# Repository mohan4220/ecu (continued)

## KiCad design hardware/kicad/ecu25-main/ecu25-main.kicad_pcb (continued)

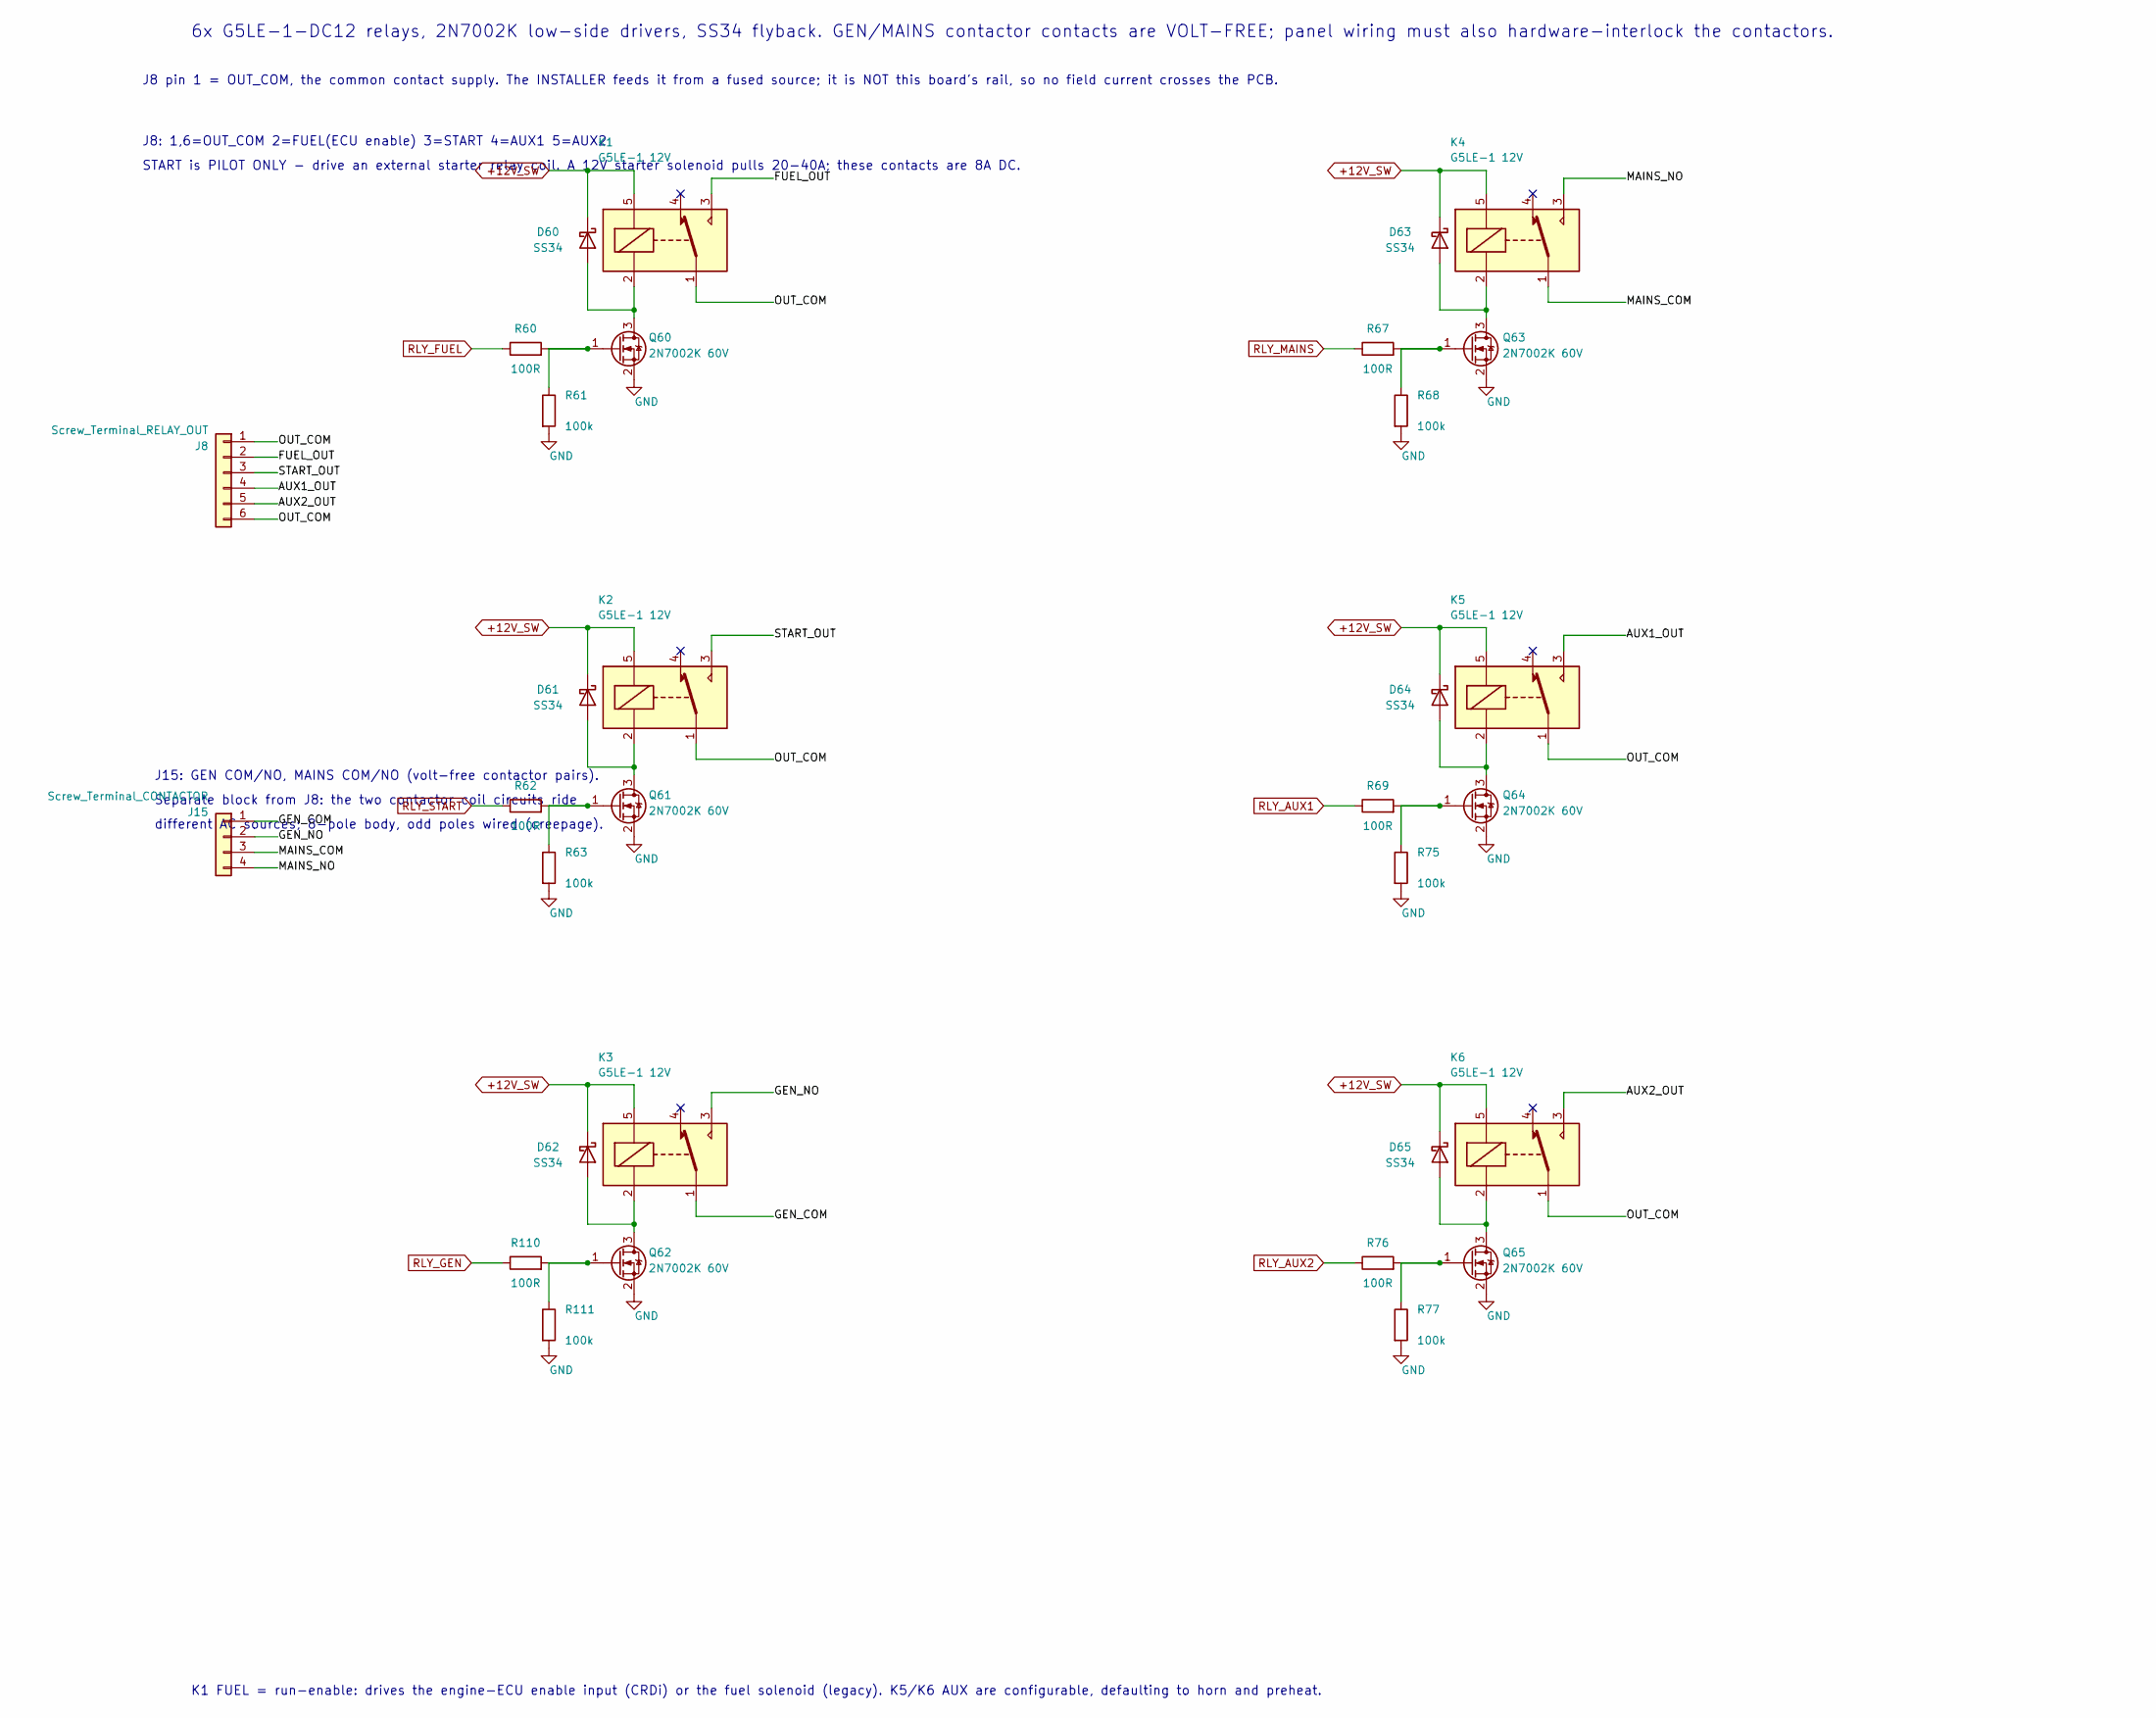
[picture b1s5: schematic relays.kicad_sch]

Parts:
D60, D61, D62, D63, D64, D65: SS34; D_SMA
J8: Screw_Terminal_RELAY_OUT; TerminalBlock_Phoenix_MKDS-3-6-5.08_1x06_P5.08mm_Horizontal
J15: Screw_Terminal_CONTACTOR; TerminalBlock_Phoenix_MKDS-3-8-5.08_1x08_P5.08mm_Horizontal
K1, K2, K3, K4, K5, K6: G5LE-1 12V; Relay_SPDT_Omron-G5LE-1
Q60, Q61, Q62, Q63, Q64, Q65: 2N7002K 60V; SOT-23
R60, R62, R67, R69, R76, R110: 100R; R_0603_1608Metric
R61, R63, R68, R75, R77, R111: 100k; R_0603_1608Metric

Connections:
+12V_SW: D60.1 (K), D61.1 (K), D62.1 (K), D63.1 (K), D64.1 (K), D65.1 (K), K1.5, K2.5, K3.5, K4.5, K5.5, K6.5; also elsewhere on the board
/Relay drivers/AUX1_OUT: J8.4, K5.3
/Relay drivers/AUX2_OUT: J8.5, K6.3
/Relay drivers/FUEL_OUT: J8.2, K1.3
/Relay drivers/GEN_COM: J15.1, K3.1
/Relay drivers/MAINS_NO: J15.4, J15.7, K4.3
/Relay drivers/OUT_COM: J8.1, J8.6, K1.1, K2.1, K5.1, K6.1
/Relay drivers/START_OUT: J8.3, K2.3
GND: Q60.2 (S), Q61.2 (S), Q62.2 (S), Q63.2 (S), Q64.2 (S), Q65.2 (S), R61.2, R63.2, R68.2, R75.2, R77.2, R111.2; also elsewhere on the board
unnamed: D60.2 (A), K1.2, Q60.3 (D)
unnamed: D61.2 (A), K2.2, Q61.3 (D)
unnamed: D62.2 (A), K3.2, Q62.3 (D)
unnamed: D63.2 (A), K4.2, Q63.3 (D)
unnamed: D64.2 (A), K5.2, Q64.3 (D)
unnamed: D65.2 (A), K6.2, Q65.3 (D)
unnamed: Q60.1 (G), R60.2, R61.1
unnamed: Q61.1 (G), R62.2, R63.1
unnamed: Q62.1 (G), R110.2, R111.1
unnamed: Q63.1 (G), R67.2, R68.1
unnamed: Q64.1 (G), R69.2, R75.1
unnamed: Q65.1 (G), R76.2, R77.1
RLY_AUX1: R69.1; also elsewhere on the board
RLY_AUX2: R76.1; also elsewhere on the board
RLY_FUEL: R60.1; also elsewhere on the board
RLY_GEN: R110.1; also elsewhere on the board
RLY_MAINS: R67.1; also elsewhere on the board
RLY_START: R62.1; also elsewhere on the board

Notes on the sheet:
6x G5LE-1-DC12 relays, 2N7002K low-side drivers, SS34 flyback. GEN/MAINS contactor contacts are VOLT-FREE; panel wiring must also hardware-interlock the contactors.
J8 pin 1 = OUT_COM, the common contact supply. The INSTALLER feeds it from a fused source; it is NOT this board's rail, so no field current crosses the PCB.
J8: 1,6=OUT_COM 2=FUEL(ECU enable) 3=START 4=AUX1 5=AUX2
START is PILOT ONLY - drive an external starter relay coil. A 12V starter solenoid pulls 20-40A; these contacts are 8A DC.
J15: GEN COM/NO, MAINS COM/NO (volt-free contactor pairs).
Separate block from J8: the two contactor coil circuits ride
different AC sources; 8-pole body, odd poles wired (creepage).
K1 FUEL = run-enable: drives the engine-ECU enable input (CRDi) or the fuel solenoid (legacy). K5/K6 AUX are configurable, defaulting to horn and preheat.

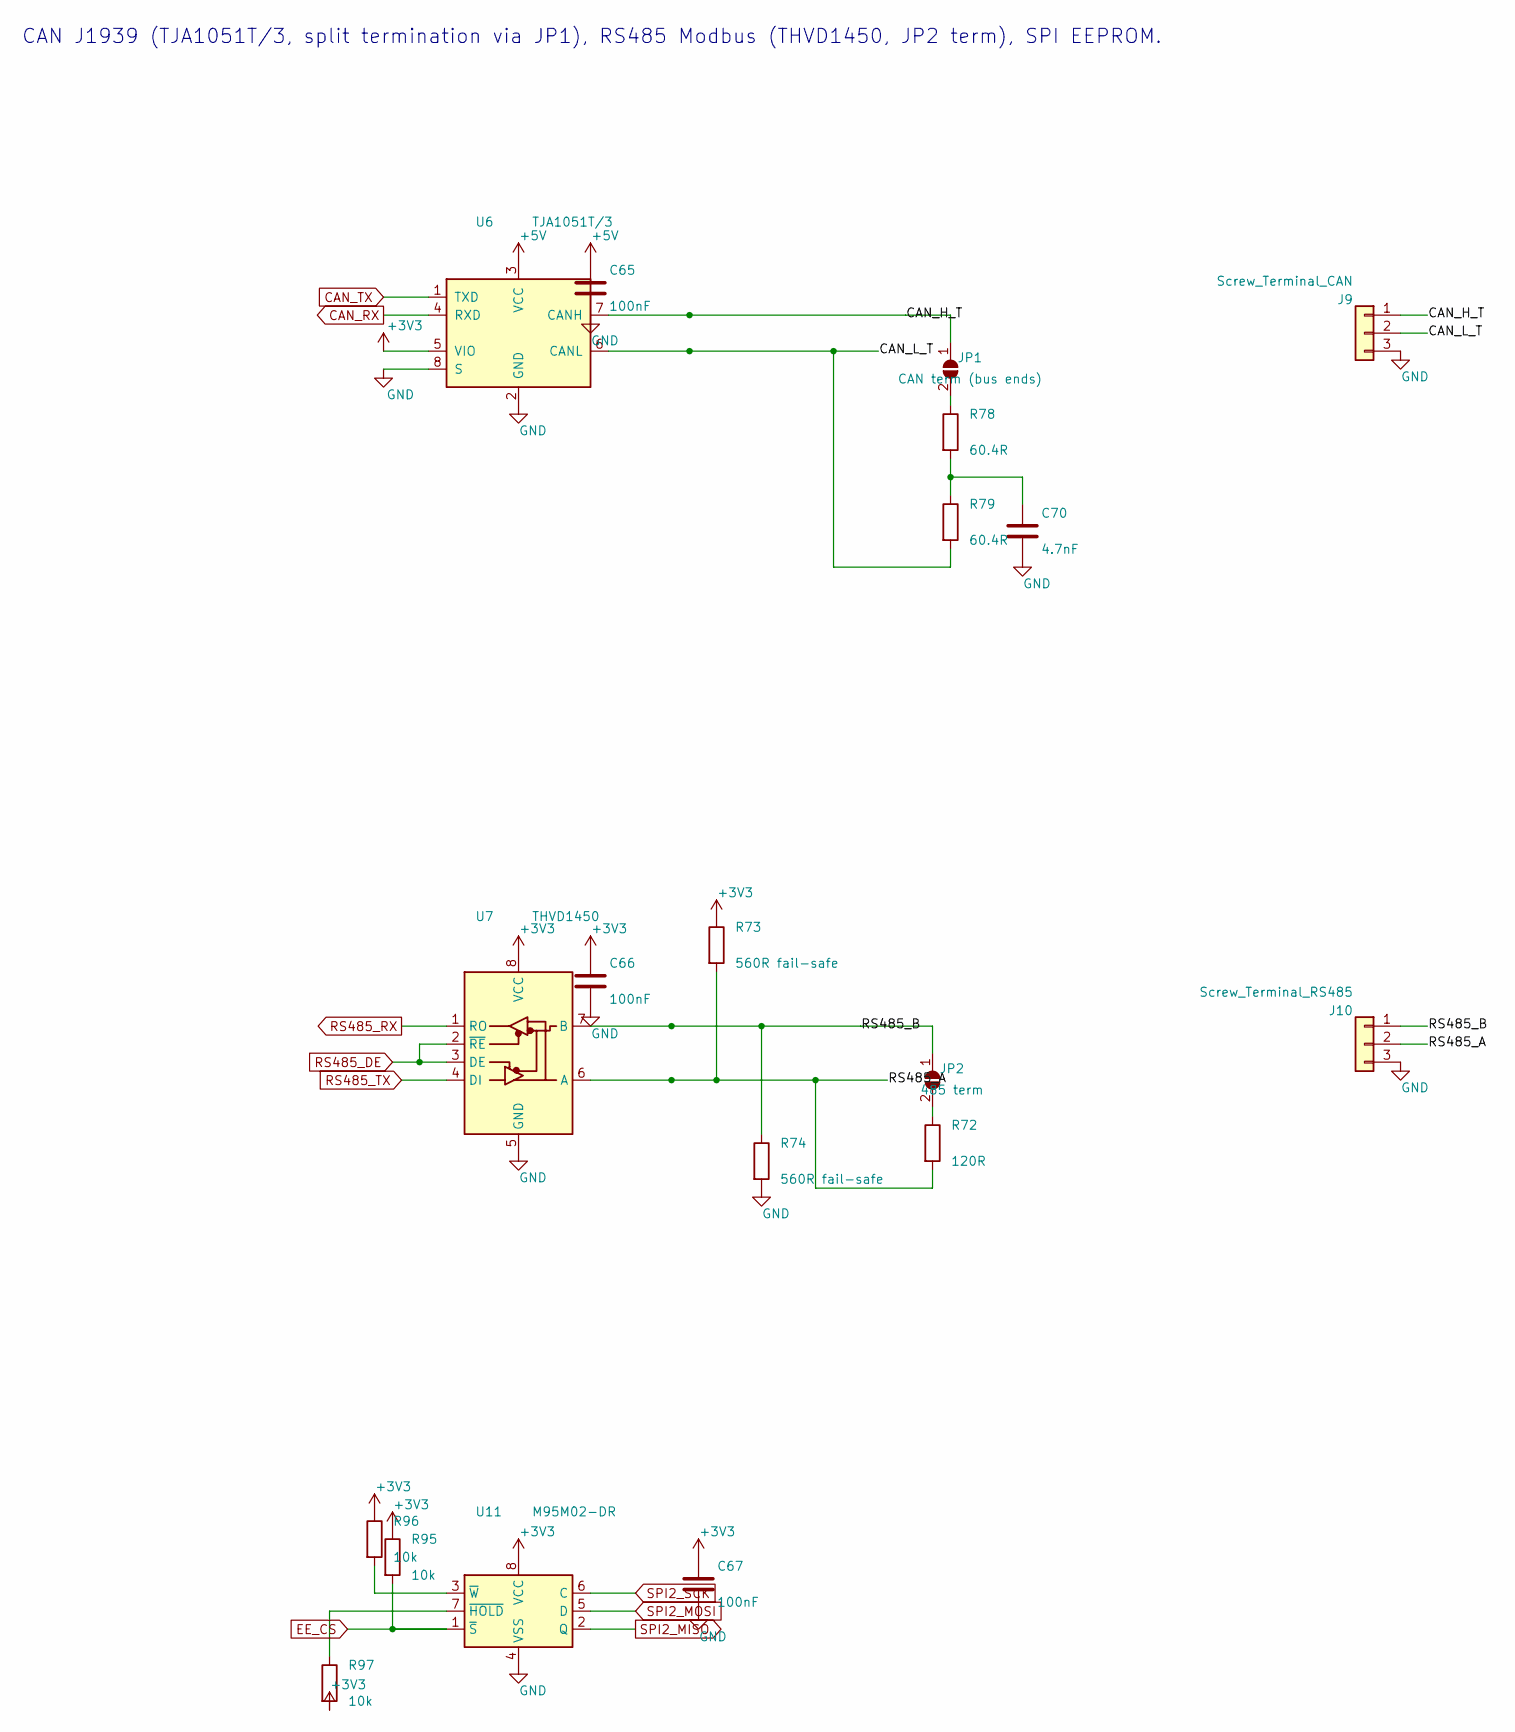
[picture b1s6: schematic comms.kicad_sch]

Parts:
C65, C66, C67: 100nF; C_0603_1608Metric
C70: 4.7nF; C_0603_1608Metric
J9: Screw_Terminal_CAN; TerminalBlock_Phoenix_MKDS-1,5-3-5.08_1x03_P5.08mm_Horizont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
J10: Screw_Terminal_RS485; TerminalBlock_Phoenix_MKDS-1,5-3-5.08_1x03_P5.08mm_Horizont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
JP1: CAN term (bus ends); SolderJumper-2_P1.3mm_Open_RoundedPad1.0x1.5mm
JP2: 485 term; SolderJumper-2_P1.3mm_Open_RoundedPad1.0x1.5mm
R72: 120R; R_0603_1608Metric
R73, R74: 560R fail-safe; R_0603_1608Metric
R78, R79: 60.4R; R_0603_1608Metric
R95, R96, R97: 10k; R_0603_1608Metric
U6: TJA1051T/3; SOIC-8_3.9x4.9mm_P1.27mm
U7: THVD1450; SOIC-8_3.9x4.9mm_P1.27mm
U11: M95M02-DR; SOIC-8_3.9x4.9mm_P1.27mm

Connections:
+3V3: C66.1, C67.1, R73.1, R95.1, R96.1, R97.2, U6.5 (VIO), U7.8 (VCC), U11.8 (VCC); also elsewhere on the board
+5V: C65.1, U6.3 (VCC); also elsewhere on the board
/Comms/CAN_H_T: J9.1, JP1.1 (A), U6.7 (CANH)
/Comms/CAN_L_T: J9.2, R79.2, U6.6 (CANL)
/Comms/RS485_A: J10.2, R72.2, R73.2, U7.6 (A)
/Comms/RS485_B: J10.1, JP2.1 (A), R74.1, U7.7 (B)
CAN_RX: U6.4 (RXD); also elsewhere on the board
CAN_TX: U6.1 (TXD); also elsewhere on the board
EE_CS: R95.2, U11.1 (~S); also elsewhere on the board
GND: C65.2, C66.2, C67.2, C70.2, J9.3, J10.3, R74.2, U6.2 (GND), U6.8 (S), U7.5 (GND), U11.4 (VSS); also elsewhere on the board
unnamed: C70.1, R78.2, R79.1
unnamed: JP1.2 (B), R78.1
unnamed: JP2.2 (B), R72.1
unnamed: R97.1, U11.7 (~HOLD)
unnamed: R96.2, U11.3 (~W)
RS485_DE: U7.2 (~RE), U7.3 (DE); also elsewhere on the board
RS485_RX: U7.1 (RO); also elsewhere on the board
RS485_TX: U7.4 (DI); also elsewhere on the board
SPI2_MISO: U11.2 (Q); also elsewhere on the board
SPI2_MOSI: U11.5 (D); also elsewhere on the board
SPI2_SCK: U11.6 (C); also elsewhere on the board

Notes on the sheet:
CAN J1939 (TJA1051T/3, split termination via JP1), RS485 Modbus (THVD1450, JP2 term), SPI EEPROM.

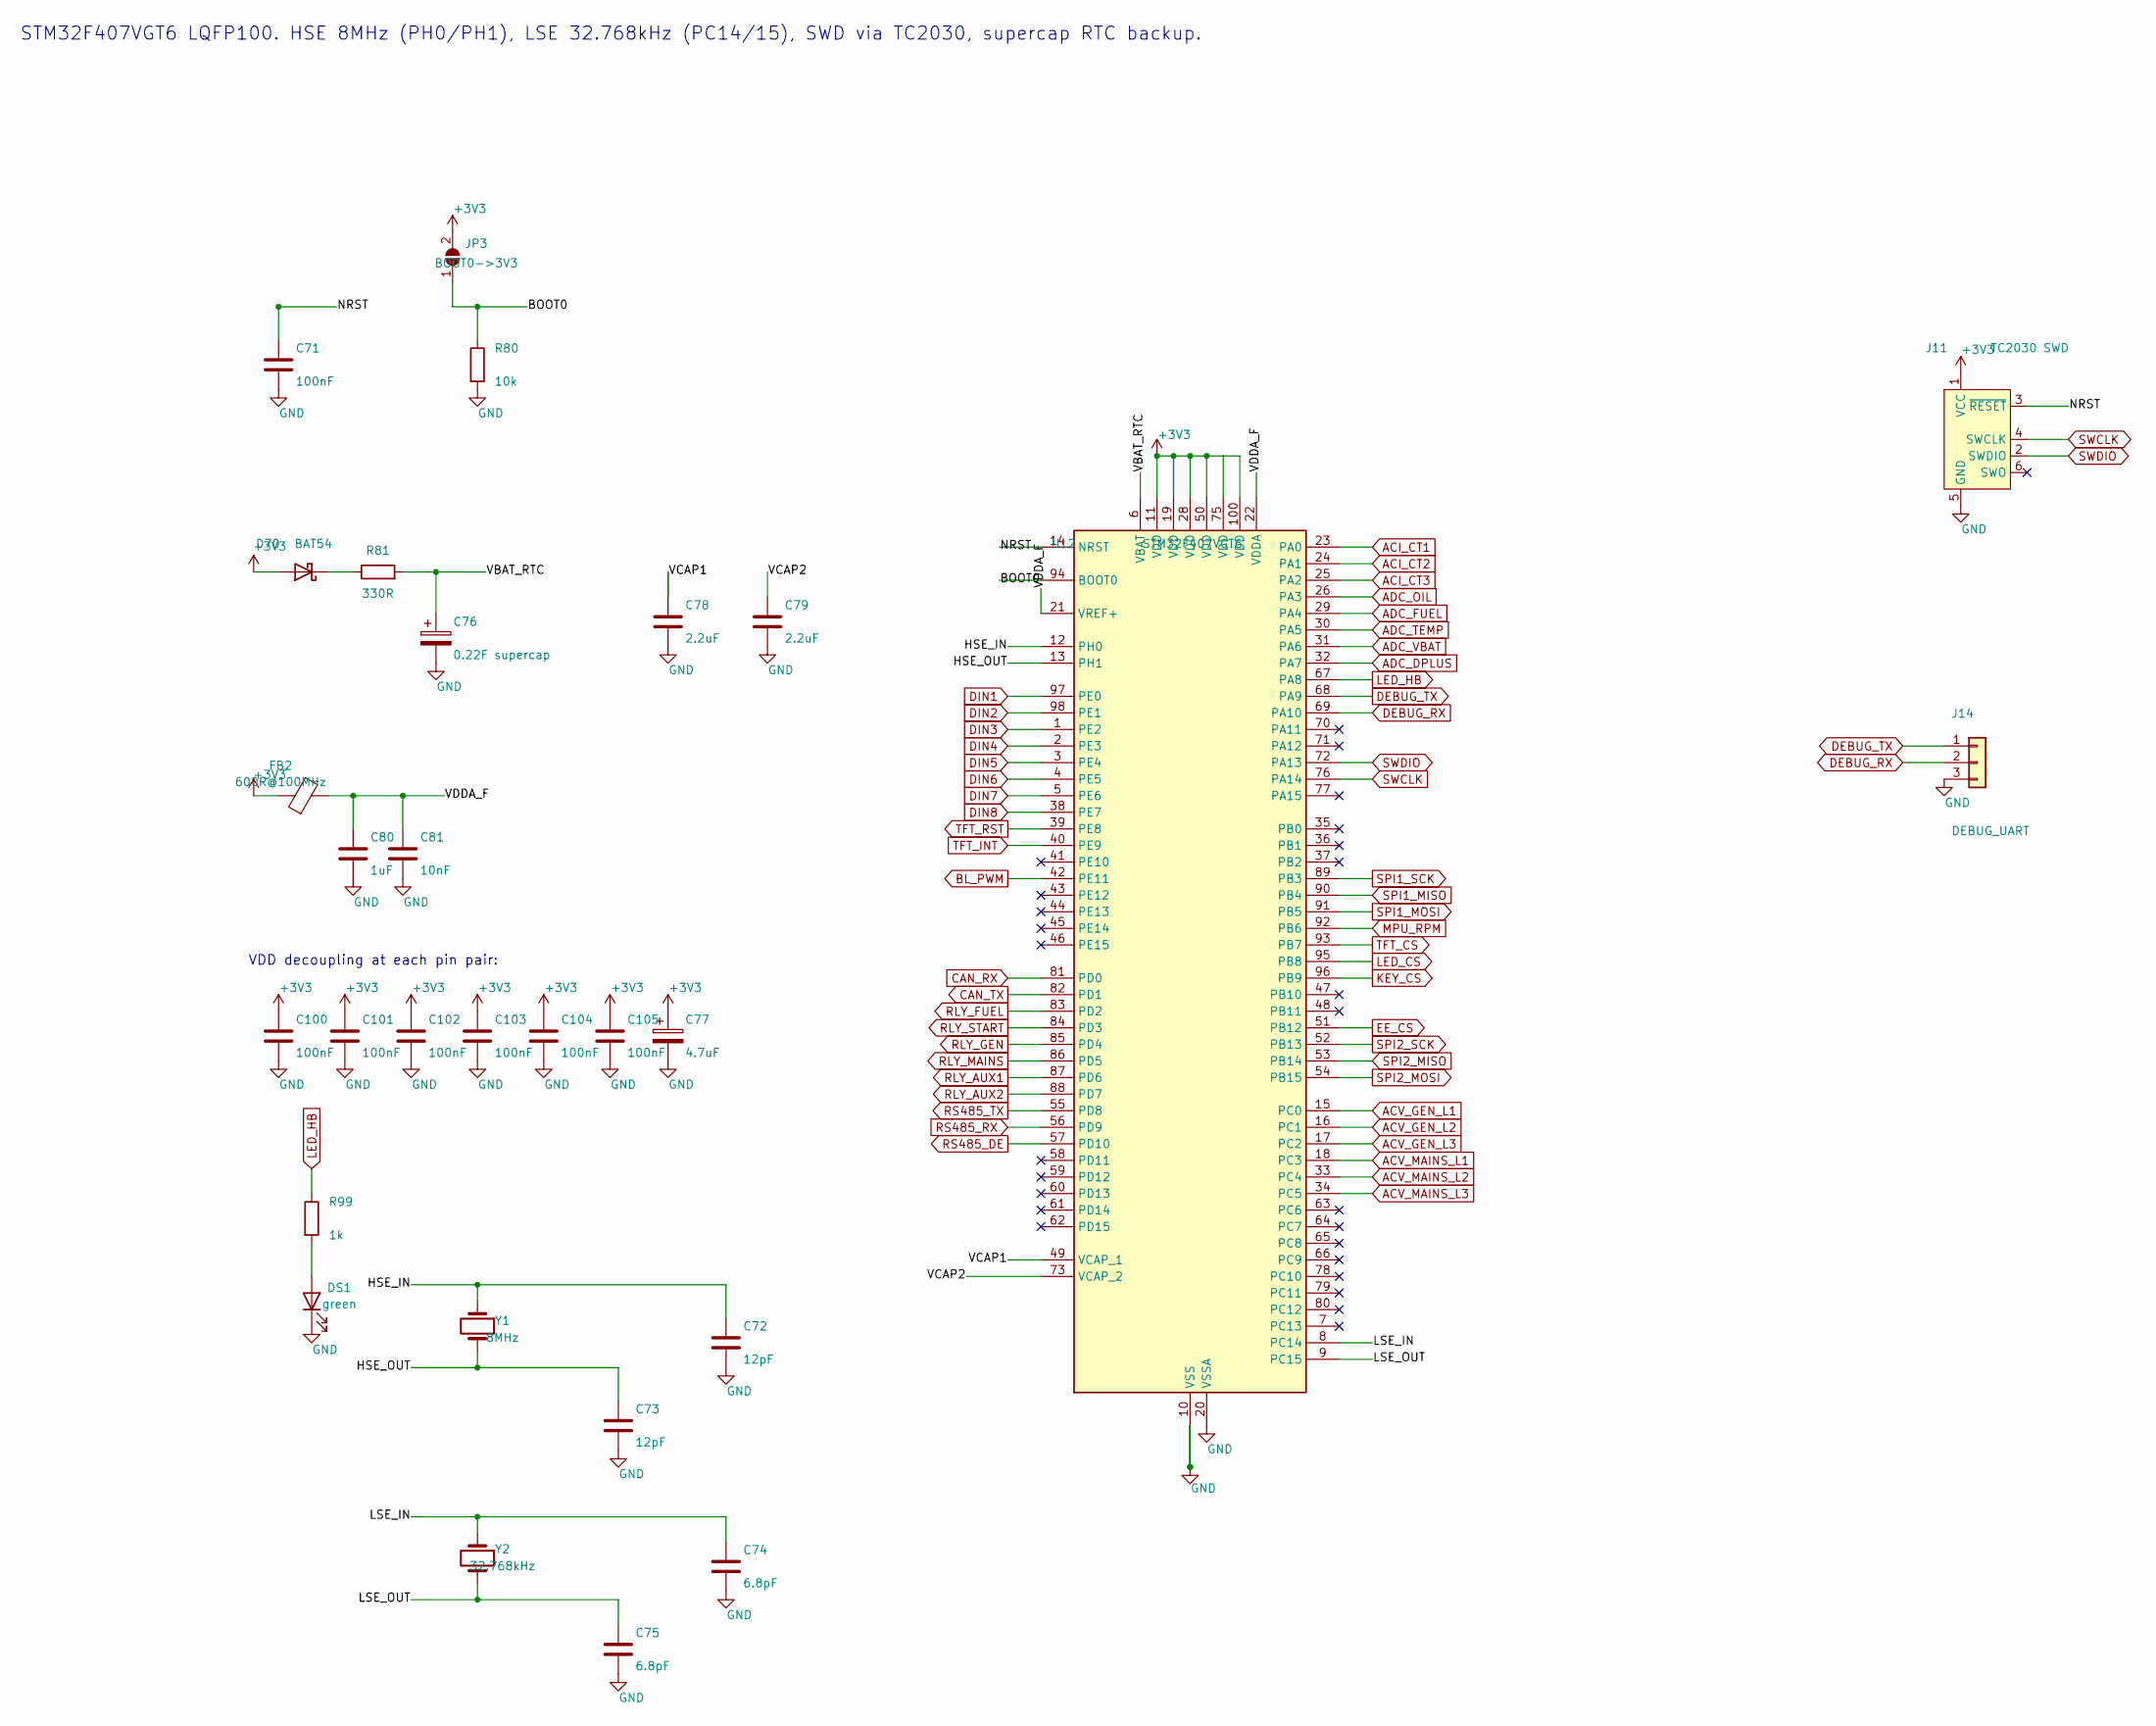
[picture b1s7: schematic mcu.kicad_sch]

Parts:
C71, C100, C101, C102, C103, C104, C105: 100nF; C_0603_1608Metric
C72, C73: 12pF; C_0603_1608Metric
C74, C75: 6.8pF; C_0603_1608Metric
C76: 0.22F supercap; CP_Radial_D10.0mm_P5.00mm
C77: 4.7uF; CP_Elec_4x5.4
C78, C79: 2.2uF; C_0603_1608Metric
C80: 1uF; C_0603_1608Metric
C81: 10nF; C_0603_1608Metric
D70: BAT54; D_SOD-123
DS1: green; LED_0805_2012Metric
FB2: 600R@100MHz; L_0603_1608Metric
J11: TC2030 SWD; Tag-Connect_TC2030-IDC-NL_2x03_P1.27mm_Vertical
J14: DEBUG_UART; PinHeader_1x03_P2.54mm_Vertical
JP3: BOOT0->3V3; SolderJumper-2_P1.3mm_Open_RoundedPad1.0x1.5mm
R80: 10k; R_0603_1608Metric
R81: 330R; R_0603_1608Metric
R99: 1k; R_0603_1608Metric
U12: STM32F407VGT6; LQFP-100_14x14mm_P0.5mm
Y1: 8MHz; Crystal_SMD_HC49-SD
Y2: 32.768kHz; Crystal_SMD_3215-2Pin_3.2x1.5mm

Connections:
+3V3: C77.1, C100.1, C101.1, C102.1, C103.1, C104.1, C105.1, D70.2 (A), FB2.1, J11.1 (VCC), JP3.2 (B), U12.11 (VDD), U12.19 (VDD), U12.28 (VDD), U12.50 (VDD), U12.75 (VDD), U12.100 (VDD); also elsewhere on the board
/MCU/BOOT0: JP3.1 (A), R80.1, U12.94 (BOOT0)
/MCU/HSE_IN: C72.1, U12.12 (PH0), Y1.1
/MCU/HSE_OUT: C73.1, U12.13 (PH1), Y1.2
/MCU/LSE_IN: C74.1, U12.8 (PC14), Y2.1
/MCU/LSE_OUT: C75.1, U12.9 (PC15), Y2.2
/MCU/NRST: C71.1, J11.3 (~RESET), U12.14 (NRST)
/MCU/VBAT_RTC: C76.1, R81.2, U12.6 (VBAT)
/MCU/VCAP1: C78.1, U12.49 (VCAP_1)
/MCU/VCAP2: C79.1, U12.73 (VCAP_2)
/MCU/VDDA_F: C80.1, C81.1, FB2.2, U12.21 (VREF+), U12.22 (VDDA)
ACI_CT1: U12.23 (PA0); also elsewhere on the board
ACI_CT2: U12.24 (PA1); also elsewhere on the board
ACI_CT3: U12.25 (PA2); also elsewhere on the board
ACV_GEN_L1: U12.15 (PC0); also elsewhere on the board
ACV_GEN_L2: U12.16 (PC1); also elsewhere on the board
ACV_GEN_L3: U12.17 (PC2); also elsewhere on the board
ACV_MAINS_L1: U12.18 (PC3); also elsewhere on the board
ACV_MAINS_L2: U12.33 (PC4); also elsewhere on the board
ACV_MAINS_L3: U12.34 (PC5); also elsewhere on the board
ADC_DPLUS: U12.32 (PA7); also elsewhere on the board
ADC_FUEL: U12.29 (PA4); also elsewhere on the board
ADC_OIL: U12.26 (PA3); also elsewhere on the board
ADC_TEMP: U12.30 (PA5); also elsewhere on the board
ADC_VBAT: U12.31 (PA6); also elsewhere on the board
BL_PWM: U12.42 (PE11); also elsewhere on the board
CAN_RX: U12.81 (PD0); also elsewhere on the board
CAN_TX: U12.82 (PD1); also elsewhere on the board
DEBUG_RX: J14.2, U12.69 (PA10)
DEBUG_TX: J14.1, U12.68 (PA9)
DIN1: U12.97 (PE0); also elsewhere on the board
DIN2: U12.98 (PE1); also elsewhere on the board
DIN3: U12.1 (PE2); also elsewhere on the board
DIN4: U12.2 (PE3); also elsewhere on the board
DIN5: U12.3 (PE4); also elsewhere on the board
DIN6: U12.4 (PE5); also elsewhere on the board
DIN7: U12.5 (PE6); also elsewhere on the board
DIN8: U12.38 (PE7); also elsewhere on the board
EE_CS: U12.51 (PB12); also elsewhere on the board
GND: C71.2, C72.2, C73.2, C74.2, C75.2, C76.2, C77.2, C78.2, C79.2, C80.2, C81.2, C100.2, C101.2, C102.2, C103.2, C104.2, C105.2, DS1.1 (K), J11.5 (GND), J14.3, R80.2, U12.10 (VSS), U12.20 (VSSA), U12.27 (VSS), U12.74 (VSS), U12.99 (VSS); also elsewhere on the board
KEY_CS: U12.96 (PB9); also elsewhere on the board
LED_CS: U12.95 (PB8); also elsewhere on the board
LED_HB: R99.1, U12.67 (PA8)
MPU_RPM: U12.92 (PB6); also elsewhere on the board
unnamed: D70.1 (K), R81.1
unnamed: DS1.2 (A), R99.2
RLY_AUX1: U12.87 (PD6); also elsewhere on the board
RLY_AUX2: U12.88 (PD7); also elsewhere on the board
RLY_FUEL: U12.83 (PD2); also elsewhere on the board
RLY_GEN: U12.85 (PD4); also elsewhere on the board
RLY_MAINS: U12.86 (PD5); also elsewhere on the board
RLY_START: U12.84 (PD3); also elsewhere on the board
RS485_DE: U12.57 (PD10); also elsewhere on the board
RS485_RX: U12.56 (PD9); also elsewhere on the board
RS485_TX: U12.55 (PD8); also elsewhere on the board
SPI1_MISO: U12.90 (PB4); also elsewhere on the board
SPI1_MOSI: U12.91 (PB5); also elsewhere on the board
SPI1_SCK: U12.89 (PB3); also elsewhere on the board
SPI2_MISO: U12.53 (PB14); also elsewhere on the board
SPI2_MOSI: U12.54 (PB15); also elsewhere on the board
SPI2_SCK: U12.52 (PB13); also elsewhere on the board
SWCLK: J11.4 (SWCLK), U12.76 (PA14)
SWDIO: J11.2 (SWDIO), U12.72 (PA13)
TFT_CS: U12.93 (PB7); also elsewhere on the board
TFT_INT: U12.40 (PE9); also elsewhere on the board
TFT_RST: U12.39 (PE8); also elsewhere on the board

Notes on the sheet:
STM32F407VGT6 LQFP100. HSE 8MHz (PH0/PH1), LSE 32.768kHz (PC14/15), SWD via TC2030, supercap RTC backup.
VDD decoupling at each pin pair:

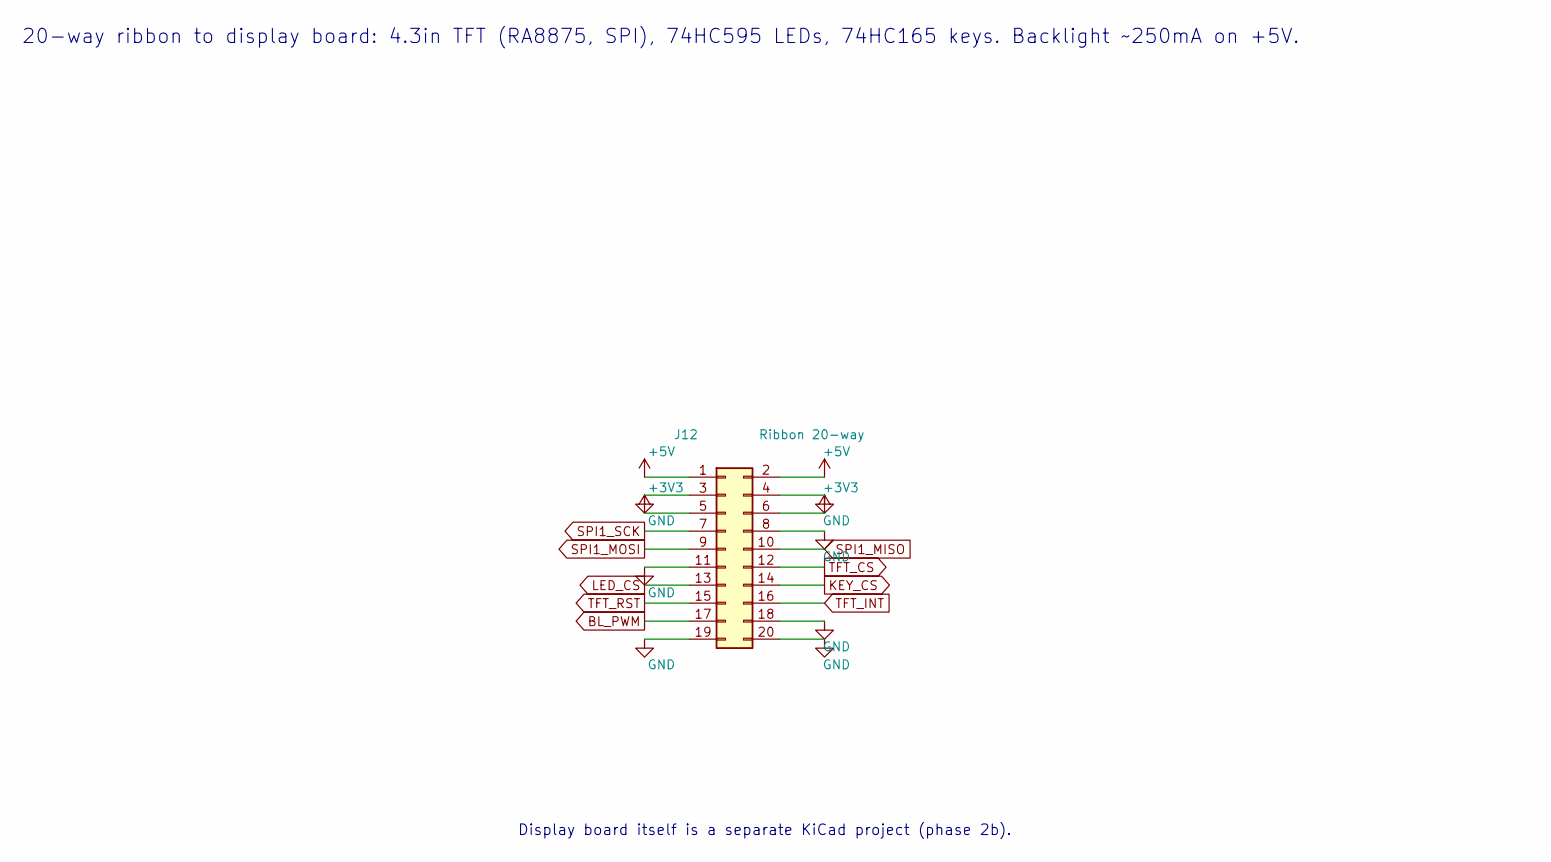
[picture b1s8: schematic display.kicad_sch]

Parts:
J12: Ribbon 20-way; IDC-Header_2x10-1MP_P2.54mm_Latch_Vertical

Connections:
+3V3: J12.5, J12.6; also elsewhere on the board
+5V: J12.1, J12.2; also elsewhere on the board
BL_PWM: J12.17; also elsewhere on the board
GND: J12.3, J12.4, J12.8, J12.11, J12.18, J12.19, J12.20, J12.MP; also elsewhere on the board
KEY_CS: J12.14; also elsewhere on the board
LED_CS: J12.13; also elsewhere on the board
SPI1_MISO: J12.10; also elsewhere on the board
SPI1_MOSI: J12.9; also elsewhere on the board
SPI1_SCK: J12.7; also elsewhere on the board
TFT_CS: J12.12; also elsewhere on the board
TFT_INT: J12.16; also elsewhere on the board
TFT_RST: J12.15; also elsewhere on the board

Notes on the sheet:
20-way ribbon to display board: 4.3in TFT (RA8875, SPI), 74HC595 LEDs, 74HC165 keys. Backlight ~250mA on +5V.
Display board itself is a separate KiCad project (phase 2b).

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
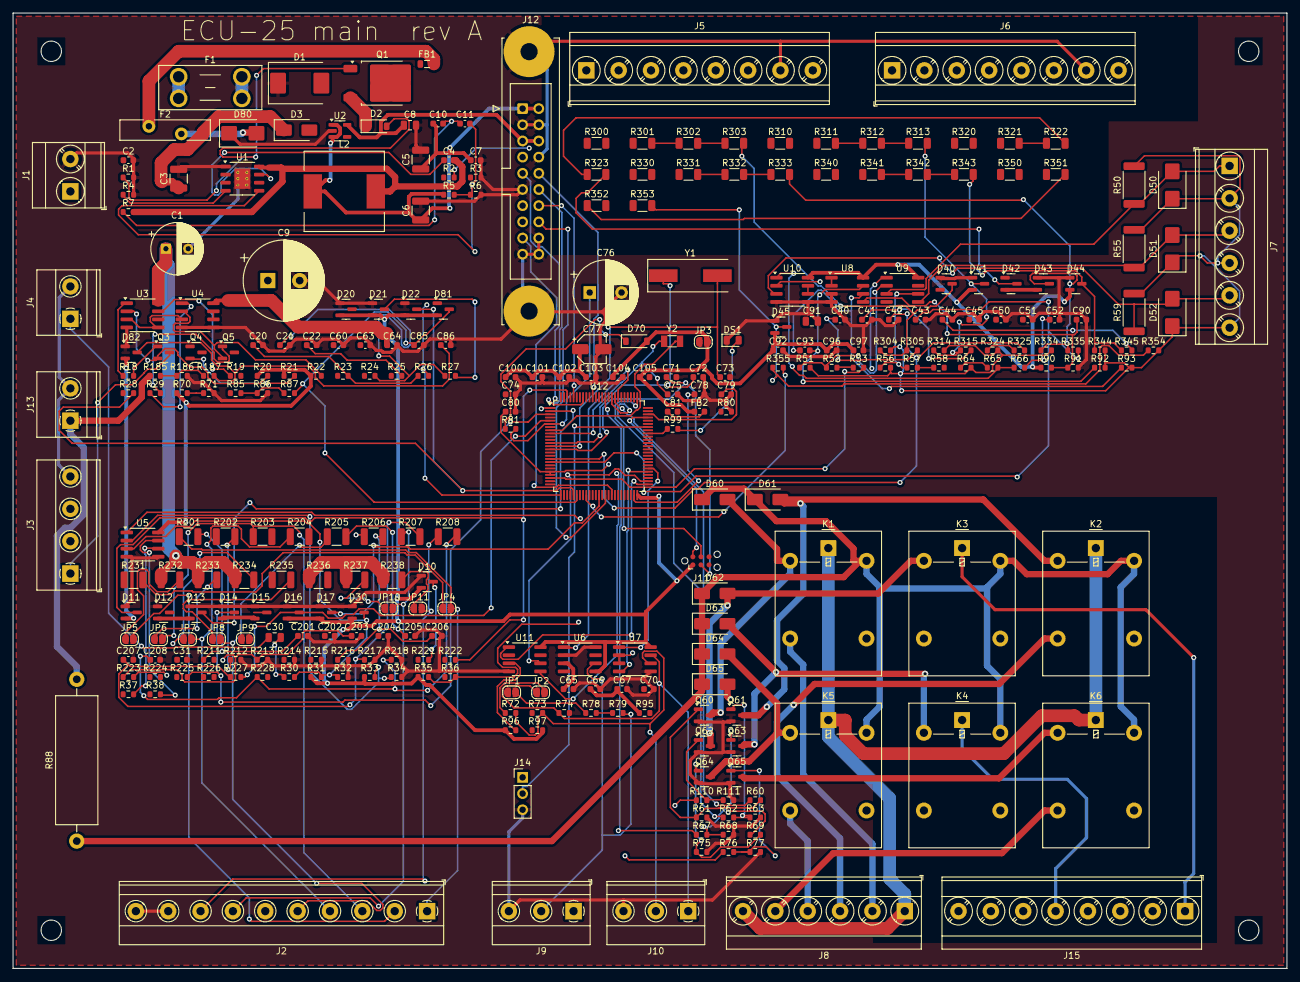
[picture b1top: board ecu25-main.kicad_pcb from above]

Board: 2 copper layers, 200.0 x 150.0 mm, 309 parts (0 on the bottom side), 205 nets.

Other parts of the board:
H1, H2, H3, H4: MountingHole_3.2mm_M3

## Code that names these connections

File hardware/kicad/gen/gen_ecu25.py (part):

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# --- input protection chain, left to right at y=50
y = 50.0
j1 = conn(s, "J1", "Screw_Terminal_BATT", 2, 25, y)
s.label(j1.pin(1), "VBAT_IN")
gnd(s, j1.pin(2))

f1 = s.place("Device:Fuse", "F1", "3A blade", (45, y), rot=90)
s.wire((40, y), f1.pin(1))
s.label((40, y), "VBAT_IN")
# D_TVS rot 90: pin2 top, pin1 bottom — rail joins the TOP pin only
d1 = s.place("Device:D_TVS", "D1", "SMCJ16CA", (55, y + 10), rot=90)
s.wire(f1.pin(2), (d1.pin(2)[0], y))          # to TVS column
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fb = u1.pin(5)
s.wire((r5.pin(2)[0], fbm), (r5.pin(2)[0] + 6, fbm))
s.junction((r5.pin(2)[0], fbm))
s.label((r5.pin(2)[0] + 6, fbm), "BUCK_FB")
s.wire(fb, (fb[0] + 4, fb[1]))
s.label((fb[0] + 4, fb[1]), "BUCK_FB")
gnd(s, r6.pin(2))
s.no_connect(u1.pin(6))  # PGOOD unused
s.wire((r5.pin(1)[0], sw[1]), (r5.pin(1)[0] + 10, sw[1]))
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#   CB >= t_settle / (3 * Rfb1) = 75us / 115k = 0.65 nF -> 1 nF C0G
_l_left = l2.pin(2) if l2.pin(2)[0] < l2.pin(1)[0] else l2.pin(1)
assert _l_left[0] - c4.pin(2)[0] > 5.08, "SW run too short to label"
s.label((c4.pin(2)[0] + 5.08, sw[1]), "BUCK_SW")
c10 = C(s, "C10", "4.7nF C0G", 200, 140)
rail(s, "+5V", c10.pin(1))
r7 = R(s, "R7", "100k 1%", 200, 152)
s.wire(c10.pin(2), r7.pin(1))
s.wire(r7.pin(2), (r7.pin(2)[0], r7.pin(2)[1] + 6))
s.label((r7.pin(2)[0], r7.pin(2)[1] + 6), "BUCK_SW")
c11 = C(s, "C11", "1nF C0G", 216, 150)
s.wire(c10.pin(2), (216, c10.pin(2)[1]))
s.junction(c10.pin(2))
s.wire((216, c10.pin(2)[1]), c11.pin(1))
s.wire(c11.pin(2), (c11.pin(2)[0], c11.pin(2)[1] + 6))
s.label((c11.pin(2)[0], c11.pin(2)[1] + 6), "BUCK_FB")

# --- LDO at y=170
u2 = s.place("Regulator_Linear:TLV75533PDBV", "U2", "TLV75533 (500mA)", (110, 170),
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s.wire((c60.pin(1)[0], m), c60.pin(1))
gnd(s, c60.pin(2))
s.wire((c60.pin(1)[0], m), (rx + 18, m))
s.label((rx + 18, m), "VREF_4V5")
s.text((rx - 15, ry - 8), "4.5V ref: 0.5V across R_set -> 8.06mA (62R) / 2.0mA (249R)", size=1.5)

j3 = conn(s, "J3", "Screw_Terminal_SENDERS", 4, 25, 100)
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    # +in = VREF_4V5, -in = emitter (feedback), out -> base via 1k
    plus5 = op.pin("3" if unit == 1 else "5")
    s.wire(plus5, (plus5[0] - 5, plus5[1]))
    s.label((plus5[0] - 5, plus5[1]), "VREF_4V5", rot=180)
    inv = op.pin("2" if unit == 1 else "6")
    s.wire(inv, (inv[0] - 3, inv[1]), (inv[0] - 3, yc - 12), (e_pin[0] + 4, yc - 12))
    s.wire((e_pin[0] + 4, yc - 12), (e_pin[0], yc - 12))
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gnd(s, c85.pin(2))
clamp99(s, "D81", (n2[0], n2[1] - 0))
s.wire(n2, (n2[0] + 8, n2[1]))
s.glabel((n2[0] + 8, n2[1]), "ADC_VBAT", shape="output")

# --- D+ excite + sense
dx, dy = 200.0, 120.0
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gnd(s, c86.pin(2))
clamp99(s, "D82", dn2)
s.wire(dn2, (dn2[0] + 8, dn2[1]))
s.glabel((dn2[0] + 8, dn2[1]), "ADC_DPLUS", shape="output")

# =================================================================
# Sheet 3 — AC SENSING (6x voltage, 3x CT, VREF_MID buffer)
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s.wire(c93.pin(2), (coutx, vm - 12), (coutx, vm))
s.junction((snap(coutx), snap(vm)))
s.wire(vrn, (vrn[0] + 8, vm))
s.glabel((vrn[0] + 8, vm), "VREF_MID", shape="output")
u8p = s.place("Amplifier_Operational:MCP6002-xSN", "U8", "MCP6002", (vx + 20, vy + 42), unit=3,
              ref_at=(vx + 17, vy + 34), val_at=(vx + 22, vy + 34))
rail(s, "+3V3", u8p.pin("8"))
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    rb = R(s, f"R{base+4}", "5.62k 1%", n1[0], yc + 10)
    s.wire(n1, rb.pin(1))
    s.wire(rb.pin(2), (rb.pin(2)[0], rb.pin(2)[1] + 3))
    s.glabel((rb.pin(2)[0], rb.pin(2)[1] + 3), "VREF_MID", rot=270)
    clamp99(s, dref, n1)
    rff = R(s, f"R{base+5}", "1k", n1[0] + 10, yc, rot=90)
    s.wire(n1, rff.pin(1))
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    s.junction((rbdn.pin(1)[0], yc))
    s.junction((rbdn.pin(2)[0], yc + 12))
    s.wire((rbdn.pin(2)[0], yc + 12), (rbdn.pin(2)[0] + 8, yc + 12))
    s.glabel((rbdn.pin(2)[0] + 8, yc + 12), "VREF_MID", shape="input")
    # amp: non-inverting gain 2 biased at VREF_MID
    op = s.place("Amplifier_Operational:MCP6002-xSN", uref, "MCP6002", (x0 + 45, yc + 2.54),
                 unit=unit, ref_at=(x0 + 42, yc + 8.5), val_at=(x0 + 48, yc + 8.5))
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    s.wire(minus, (minus[0] - 3, minus[1]))
    s.wire((minus[0] - 3, minus[1]), (rg1.pin(1)[0], minus[1] + 2) if False else (minus[0] - 3, minus[1]))
    s.wire_v_then_h((minus[0] - 3, minus[1]), rg1.pin(1))
    s.glabel((rg1.pin(2)[0], rg1.pin(2)[1] + 3), "VREF_MID", rot=270)
    s.wire(rg1.pin(2), (rg1.pin(2)[0], rg1.pin(2)[1] + 3))
    rg2 = R(s, r52, "10k 1%", minus[0] + 5, minus[1] - 9, rot=90)
    s.wire((minus[0] - 3, minus[1]), (minus[0] - 3, rg2.pin(1)[1]), rg2.pin(1))
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s.text((mx - 5, my - 14), "MPU / magnetic pickup RPM input", size=1.7)
j4 = conn(s, "J4", "Screw_Terminal_MPU", 2, mx, my + 30)
s.wire(j4.pin(1), (j4.pin(1)[0] + 4, j4.pin(1)[1]))
s.label((j4.pin(1)[0] + 4, j4.pin(1)[1]), "MPU_P")
gnd(s, j4.pin(2))
x0 = mx + 20
s.label((x0 - 6, my), "MPU_P", rot=180)
c30 = C(s, "C30", "100nF 100V", x0 + 4, my, rot=90)
s.wire((x0 - 6, my), c30.pin(1))
r30 = R(s, "R30", "10k", c30.pin(2)[0] + 8, my, rot=90)
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s.wire(r36.pin(1), (n2[0], my - 22), (n2[0], n2[1]))
s.junction(n2)
s.wire(o, (o[0] + 8, o[1]))
s.glabel((o[0] + 8, o[1]), "MPU_RPM", shape="output")
# LM2903 power unit at +5V (VICM limit), unused unit 2 tied off
u5p = s.place("Comparator:LM2903", "U5", "LM2903", (mx + 20, my + 60), unit=3,
              ref_at=(mx + 17, my + 52), val_at=(mx + 22, my + 52))
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                 " also hardware-interlock the contactors.", size=2.0)

j8 = conn(s, "J8", "Screw_Terminal_RELAY_OUT", 6, 25, 90)
s.text((12, 26), "J8 pin 1 = OUT_COM, the common contact supply. The INSTALLER"
                 " feeds it from a fused source; it is NOT this board's rail, so"
                 " no field current crosses the PCB.", size=1.5)
s.text((12, 36), "J8: 1,6=OUT_COM 2=FUEL(ECU enable) 3=START 4=AUX1 5=AUX2", size=1.5)
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        s.label((lx, ycom), f"{name}_COM")
        s.label((lx, yno), f"{name}_NO")
    else:
        s.label((lx, ycom), "OUT_COM")
        s.label((lx, yno), f"{name}_OUT")

# terminal wiring: J8 = common supply + 4 dry NO outputs, J15 = volt-free pairs
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u6 = s.place("Interface_CAN_LIN:TJA1051T-3", "U6", "TJA1051T/3", (90, 60),
             ref_at=(84, 44), val_at=(92, 44))
s.wire(u6.pin(1), (u6.pin(1)[0] - 6, u6.pin(1)[1]))
s.glabel((u6.pin(1)[0] - 6, u6.pin(1)[1]), "CAN_TX", rot=180, shape="input")
s.wire(u6.pin(4), (u6.pin(4)[0] - 6, u6.pin(4)[1]))
s.glabel((u6.pin(4)[0] - 6, u6.pin(4)[1]), "CAN_RX", rot=180, shape="output")
s.wire(u6.pin(5), (u6.pin(5)[0] - 6, u6.pin(5)[1]))
rail(s, "+3V3", (u6.pin(5)[0] - 6, u6.pin(5)[1]))
gnd(s, (u6.pin(8)[0] - 6, u6.pin(8)[1] + 0))
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# split termination hangs BELOW the CANL row via a solder jumper:
# CANH row -> down (right of the bus labels) -> JP1 -> R78 -> R79 -> up to CANL
s.wire((hx, canh[1]), (hx + 30, canh[1]))
s.label((hx + 30, canh[1]), "CAN_H_T")
s.wire((hx, canl[1]), (hx + 26, canl[1]))
s.label((hx + 26, canl[1]), "CAN_L_T")
tx = hx + 36
s.wire((hx + 30, canh[1]), (tx, canh[1]))   # extend H bus to the drop column
jp1 = s.place("Jumper:SolderJumper_2_Open", "JP1", "CAN term (bus ends)",
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s.junction((lx, canl[1]))
j9 = conn(s, "J9", "Screw_Terminal_CAN", 3, 210, canh[1] + 2)
s.wire(j9.pin(1), (j9.pin(1)[0] + 4, j9.pin(1)[1]))
s.label((j9.pin(1)[0] + 4, j9.pin(1)[1]), "CAN_H_T")
s.wire(j9.pin(2), (j9.pin(2)[0] + 4, j9.pin(2)[1]))
s.label((j9.pin(2)[0] + 4, j9.pin(2)[1]), "CAN_L_T")
gnd(s, j9.pin(3))

# RS485
u7 = s.place("Interface_UART:MAX3485", "U7", "THVD1450", (90, 160),
             ref_at=(84, 142), val_at=(92, 142))
s.wire(u7.pin(4), (u7.pin(4)[0] - 6, u7.pin(4)[1]))
s.glabel((u7.pin(4)[0] - 6, u7.pin(4)[1]), "RS485_TX", rot=180, shape="input")
s.wire(u7.pin(1), (u7.pin(1)[0] - 6, u7.pin(1)[1]))
s.glabel((u7.pin(1)[0] - 6, u7.pin(1)[1]), "RS485_RX", rot=180, shape="output")
# DE and /RE tied together to one GPIO
s.wire(u7.pin(2), (u7.pin(2)[0] - 4, u7.pin(2)[1]), (u7.pin(2)[0] - 4, u7.pin(3)[1]), u7.pin(3))
s.junction((u7.pin(2)[0] - 4, u7.pin(3)[1]))
s.wire((u7.pin(2)[0] - 4, u7.pin(3)[1]), (u7.pin(3)[0] - 8, u7.pin(3)[1]))
s.glabel((u7.pin(3)[0] - 8, u7.pin(3)[1]), "RS485_DE", rot=180, shape="input")
rail(s, "+3V3", u7.pin(8))
c66 = C(s, "C66", "100nF", u7.pin(8)[0] + 10, u7.pin(8)[1] + 4)
rail(s, "+3V3", c66.pin(1))
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gnd(s, r74.pin(2))
# bus rows out to labels
s.wire((ax, b_[1]), (ax + 26, b_[1]))
s.label((ax + 26, b_[1]), "RS485_B")
s.wire((ax, a_[1]), (ax + 30, a_[1]))
s.label((ax + 30, a_[1]), "RS485_A")
# termination JP2 + R72 hang below on their own drop column (right of labels)
tx2 = ax + 36
s.wire((ax + 26, b_[1]), (tx2, b_[1]))   # extend B row to drop column
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s.junction((lx2, a_[1]))
j10 = conn(s, "J10", "Screw_Terminal_RS485", 3, 210, b_[1] + 2)
s.wire(j10.pin(1), (j10.pin(1)[0] + 4, j10.pin(1)[1]))
s.label((j10.pin(1)[0] + 4, j10.pin(1)[1]), "RS485_B")
s.wire(j10.pin(2), (j10.pin(2)[0] + 4, j10.pin(2)[1]))
s.label((j10.pin(2)[0] + 4, j10.pin(2)[1]), "RS485_A")
gnd(s, j10.pin(3))

# EEPROM
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s.wire(r95.pin(2), (r95.pin(2)[0], cs[1]), cs)
s.junction((r95.pin(2)[0], cs[1]))
s.wire(cs, (cs[0] - 14, cs[1]))
s.glabel((cs[0] - 14, cs[1]), "EE_CS", rot=180, shape="input")
for pin, net, shape in (("3", "WP_TIE", None), ("7", "HOLD_TIE", None)):
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
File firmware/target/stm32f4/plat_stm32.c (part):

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 * Pin assignment comes from hardware/kicad/gen/gen_ecu25.py (PINMAP) and is
 * mirrored in docs/io-map.md. If you change one, change all three.
 *
 *   ADC1 IN10-15  PC0-PC5   gen L1-3, mains L1-3
 *   ADC1 IN0-2    PA0-PA2   CT1-3
 *   ADC1 IN3-7    PA3-PA7   oil, fuel, temp, vbat, D+
 *   TIM2 TRGO               3200 Hz conversion trigger
 *   DMA2 Stream0 Ch0        ADC1 -> ring of sample sets
 *   TIM4_CH1      PB6       magnetic pickup period capture
 *   TIM1_CH2      PE11      backlight PWM
 *   USART3        PD8/PD9   Modbus RTU, DE on PD10
 *   CAN1          PD0/PD1   J1939, 250 kbit/s
 *   GPIOD 2-7               relay drivers K1-K6
 *   GPIOE 0-7               digital inputs DIN1-8
 *   GPIOA 8                 heartbeat LED
 *
 * NOT YET VERIFIED ON SILICON. This compiles and the register sequences
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 * enum order in ac_sense.h, because ac_sample() copies them straight across.
 */
static const uint8_t ADC_SEQ[ADC_SEQ_LEN] = {
    10, 11, 12,   /* AC_GEN_L1..L3   PC0-PC2 */
    13, 14, 15,   /* AC_MAINS_L1..L3 PC3-PC5 */
    0, 1, 2,      /* AC_I_L1..L3     PA0-PA2 */
    3, 4, 5, 6, 7 /* oil, fuel, temp, vbat, D+ */
};

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    /* One BSRR write drives all six coils, so the relays change together
     * rather than in a staggered sequence a scope would catch. */
    const bool on[6] = {
        o->run_enable,      /* PD2 K1 FUEL  */
        o->starter,         /* PD3 K2 START */
        o->gen_contactor,   /* PD4 K3 GEN   */
        o->mains_contactor, /* PD5 K4 MAINS */
        o->aux1,            /* PD6 K5 AUX1  */
        o->aux2,            /* PD7 K6 AUX2  */
    };
    uint32_t bsrr = 0;
    for (uint32_t i = 0; i < 6; i++) {
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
